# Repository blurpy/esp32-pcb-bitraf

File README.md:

# esp32-pcb-bitraf

ESP32 S2 Mini Development Board PCB created with KiCad 6 at Bitraf workshop, to be ordered from PCBWay.

Reference PCB for the workshop available here: https://github.com/jenschr/ESP32-workshop-files

Inspired by the official development board [ESP32-S2-DevKitM-1](https://docs.espressif.com/projects/esp-idf/en/v4.4/esp32s2/hw-reference/esp32s2/user-guide-devkitm-1-v1.html).

### Features

* Reset switch
* Boot switch for entering programming mode
* Power LED
* General purpose LED
* [DotStar LED](https://learn.adafruit.com/adafruit-dotstar-leds/overview)
* USB-C for power and programming
* Fits on a breadboard

### Board

### Schematic

### Bill of materials

Also available as an [interactive bom](https://blurpy.github.io/esp32-pcb-bitraf/bom/ibom.html).

| Item | Qty | Reference(s)   | Value                   | Type             | Footprint                              | Datasheet                                                                                                     |
|------|-----|----------------|-------------------------|------------------|----------------------------------------|---------------------------------------------------------------------------------------------------------------|
| 1    | 2   | BOOT1, RESET1  | SW_Push                 | Switch           | SW_SPST_Panasonic_EVQPL_3PL_5PL_PT_A08 | ~                                                                                                             |
| 2    | 4   | C1, C2, C3, C5 | 0.1uF                   | Capacitor        | 0603_1608Metric                        | ~                                                                                                             |
| 3    | 1   | C4             | 10uF                    | Capacitor        | 0805_2012Metric                        | ~                                                                                                             |
| 4    | 2   | D1, D2         | LED                     | LED              | 0603_1608Metric                        | ~                                                                                                             |
| 5    | 1   | D3             | APA102-2020             | DotStar LED      | APA102-2020                            | https://www.led-color.com/upload/201604/APA102-2020%20SMD%20LED.pdf                                           |
| 6    | 2   | J1, J3         | Conn_01x20_Male         | Header           | PinHeader_1x20_P2.54mm_Vertical        | ~                                                                                                             |
| 7    | 1   | J2             | USB_C_Receptacle_USB2.0 | USB-C Connector  | TYPE-C-31-M-12                         | https://www.usb.org/sites/default/files/documents/usb_type-c.zip                                              |
| 8    | 2   | R1, R2         | 10K                     | Resistor         | 0603_1608Metric                        | ~                                                                                                             |
| 9    | 2   | R3, R4         | 5.1K                    | Resistor         | 0603_1608Metric                        | ~                                                                                                             |
| 10   | 2   | R5, R6         | 33R                     | Resistor         | 0603_1608Metric                        | ~                                                                                                             |
| 11   | 2   | R7, R8         | 1K                      | Resistor         | 0603_1608Metric                        | ~                                                                                                             |
| 12   | 1   | U1             | ESP32-S2-M              | Microcontroller  | ESP32-S2-MINI-1-N4                     | https://www.espressif.com/sites/default/files/documentation/esp32-s2-mini-1_esp32-s2-mini-1u_datasheet_en.pdf |
| 13   | 1   | U2             | LM1117-3.3              | Linear Regulator | SOT-223                                | https://www.ti.com/lit/ds/symlink/lm1117.pdf                                                                  |

### Libraries

* [USB TYPE-C-31-M-12 from Korean Hroparts Elec @ LCSC](https://github.com/jenschr/USB-C-Connectors)
  *  Available here: https://lcsc.com/product-detail/USB-Connectors_Korean-Hroparts-Elec-TYPE-C-31-M-12_C165948.html
* [Espressif Systems ESP32-S2-MINI-1-N4](https://app.ultralibrarian.com/details/e7064ac7-afcb-11eb-9033-0a34d6323d74/Espressif-Systems/ESP32-S2-MINI-1-N4)
  * Symbol Pin Ordering: Functional
  * Footprint Units: English (mil)

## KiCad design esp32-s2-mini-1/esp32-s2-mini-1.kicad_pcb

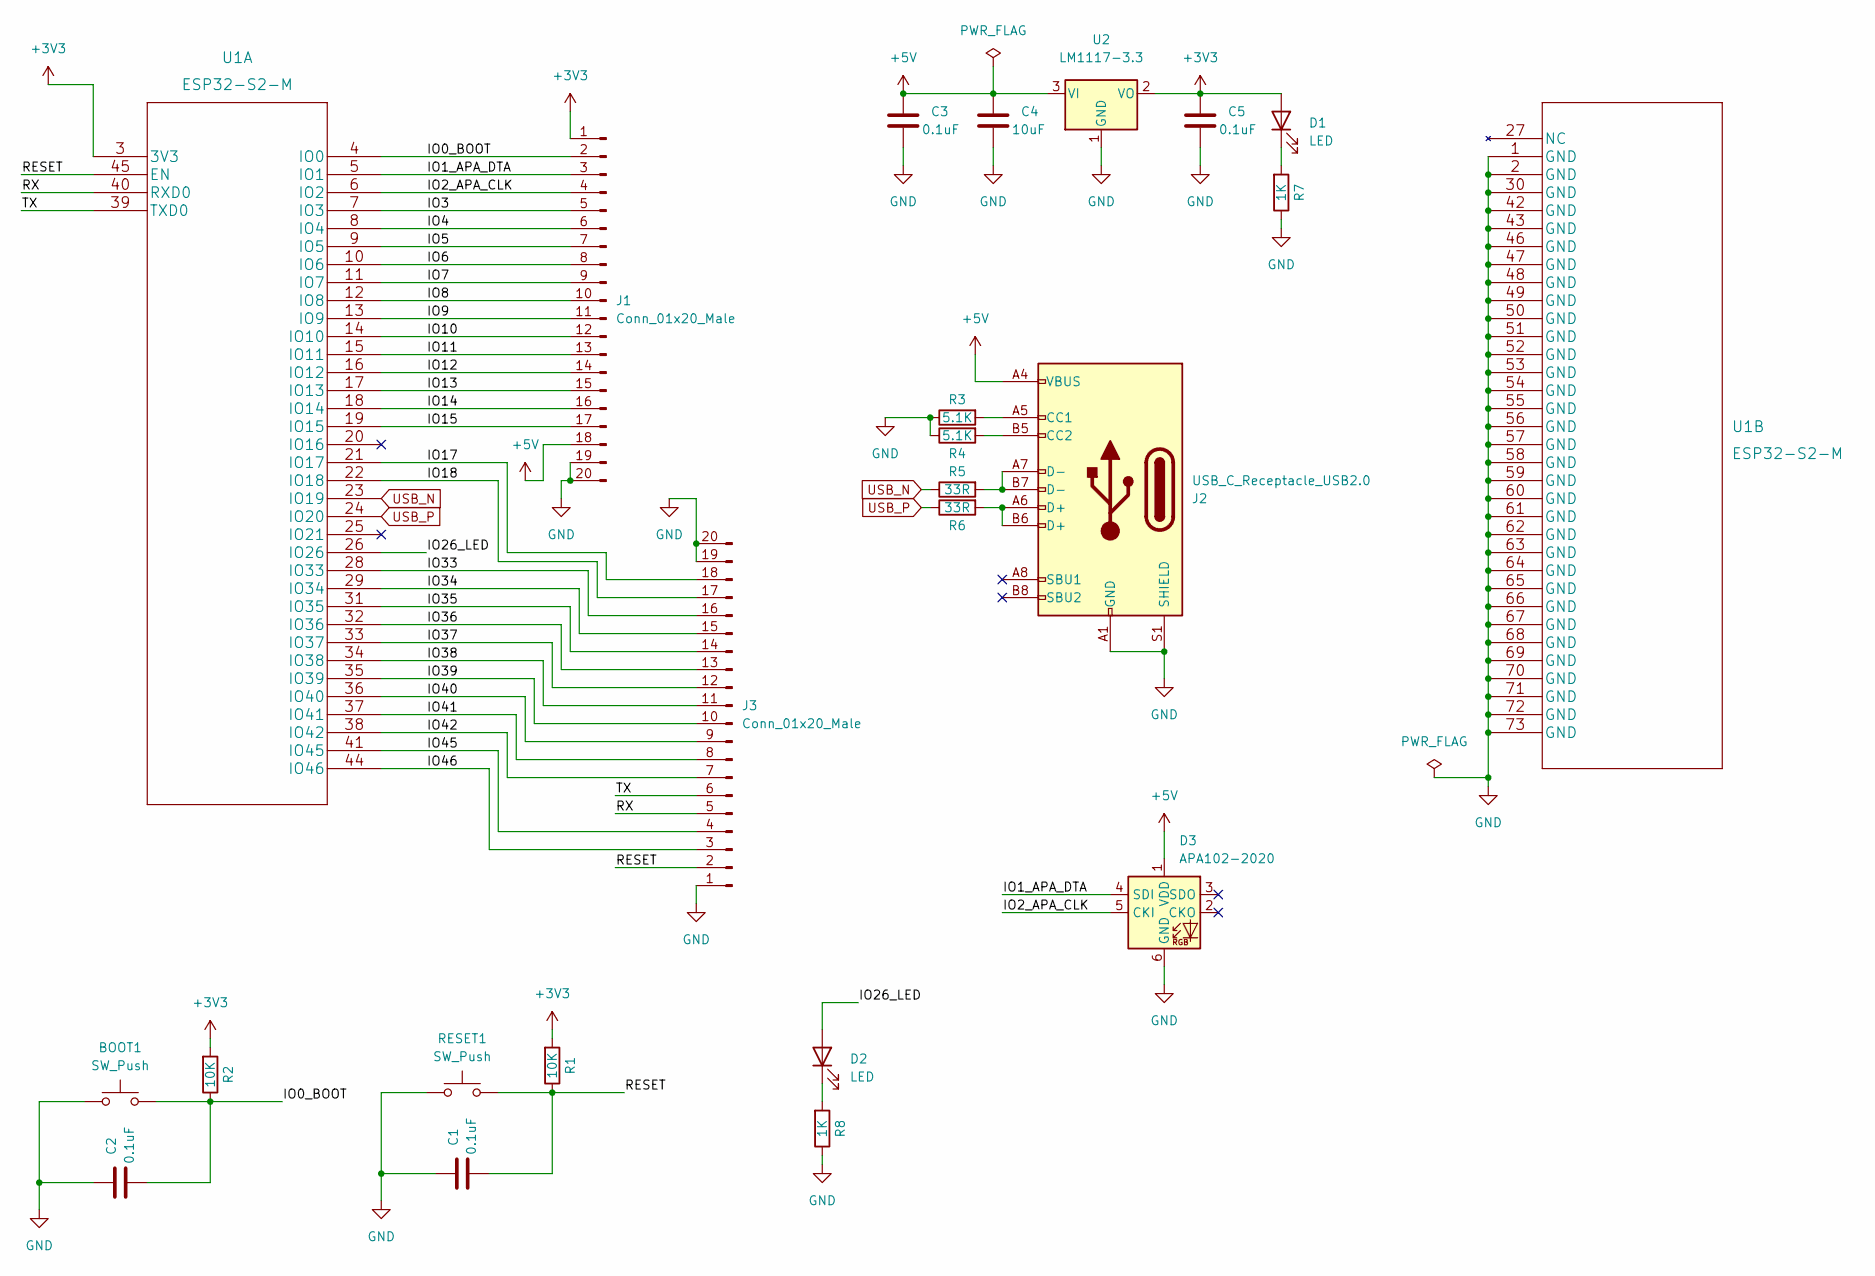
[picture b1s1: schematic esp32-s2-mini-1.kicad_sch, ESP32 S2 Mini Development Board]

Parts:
BOOT1: SW_Push; SW_SPST_Panasonic_EVQPL_3PL_5PL_PT_A08
C1, C2, C3, C5: 0.1uF; C_0603_1608Metric
C4: 10uF; C_0805_2012Metric
D1, D2: LED; LED_0603_1608Metric
D3: APA102-2020; LED-APA102-2020
J1, J3: Conn_01x20_Male; PinHeader_1x20_P2.54mm_Vertical
J2: USB_C_Receptacle_USB2.0; TYPE-C-31-M-12
R1, R2: 10K; R_0603_1608Metric
R3, R4: 5.1K; R_0603_1608Metric
R5, R6: 33R; R_0603_1608Metric
R7, R8: 1K; R_0603_1608Metric
RESET1: SW_Push; SW_SPST_Panasonic_EVQPL_3PL_5PL_PT_A08
U1: ESP32-S2-M; ESP32-S2-MINI-1-N4
U2: LM1117-3.3; SOT-223

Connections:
+3V3: C5.1, D1.2 (A), J1.1, R1.2, R2.2, U1.3 (3V3), U2.2 (VO)
+5V: C3.1, C4.1, D3.1 (VDD), J1.18, J2.A4 (VBUS), J2.A9 (VBUS), J2.B4 (VBUS), J2.B9 (VBUS), U2.3 (VI)
/IO0_BOOT: BOOT1.2, C2.2, J1.2, R2.1, U1.4 (IO0)
/IO1_APA_DTA: D3.4 (SDI), J1.3, U1.5 (IO1)
/IO2_APA_CLK: D3.5 (CKI), J1.4, U1.6 (IO2)
/IO3: J1.5, U1.7 (IO3)
/IO4: J1.6, U1.8 (IO4)
/IO5: J1.7, U1.9 (IO5)
/IO6: J1.8, U1.10 (IO6)
/IO7: J1.9, U1.11 (IO7)
/IO8: J1.10, U1.12 (IO8)
/IO9: J1.11, U1.13 (IO9)
/IO10: J1.12, U1.14 (IO10)
/IO11: J1.13, U1.15 (IO11)
/IO12: J1.14, U1.16 (IO12)
/IO13: J1.15, U1.17 (IO13)
/IO14: J1.16, U1.18 (IO14)
/IO15: J1.17, U1.19 (IO15)
/IO17: J3.18, U1.21 (IO17)
/IO18: J3.17, U1.22 (IO18)
/IO26_LED: D2.2 (A), U1.26 (IO26)
/IO33: J3.16, U1.28 (IO33)
/IO34: J3.15, U1.29 (IO34)
/IO35: J3.14, U1.31 (IO35)
/IO36: J3.13, U1.32 (IO36)
/IO37: J3.12, U1.33 (IO37)
/IO38: J3.11, U1.34 (IO38)
/IO39: J3.10, U1.35 (IO39)
/IO40: J3.9, U1.36 (IO40)
/IO41: J3.8, U1.37 (IO41)
/IO42: J3.7, U1.38 (IO42)
/IO45: J3.4, U1.41 (IO45)
/IO46: J3.3, U1.44 (IO46)
/RESET: C1.2, J3.2, R1.1, RESET1.2, U1.45 (EN)
/RX: J3.5, U1.40 (RXD0)
/TX: J3.6, U1.39 (TXD0)
GND: BOOT1.1, C1.1, C2.1, C3.2, C4.2, C5.2, D3.6 (GND), J1.19, J1.20, J2.A1 (GND), J2.A12 (GND), J2.B1 (GND), J2.B12 (GND), J2.S1 (SHIELD), J3.1, J3.19, J3.20, R3.1, R4.1, R7.1, R8.1, RESET1.1, U1.1 (GND), U1.2 (GND), U1.30 (GND), U1.42 (GND), U1.43 (GND), U1.46 (GND), U1.47 (GND), U1.48 (GND), U1.49 (GND), U1.50 (GND), U1.51 (GND), U1.52 (GND), U1.53 (GND), U1.54 (GND), U1.55 (GND), U1.56 (GND), U1.57 (GND), U1.58 (GND), U1.59 (GND), U1.60 (GND), U1.61 (GND), U1.62 (GND), U1.63 (GND), U1.64 (GND), U1.65 (GND), U1.66 (GND), U1.67 (GND), U1.68 (GND), U1.69 (GND), U1.70 (GND), U1.71 (GND), U1.72 (GND), U1.73 (GND), U2.1 (GND)
unnamed: D1.1 (K), R7.2
unnamed: D2.1 (K), R8.2
unnamed: J2.A5 (CC1), R3.2
unnamed: J2.A6 (D+), J2.B6 (D+), R6.2
unnamed: J2.A7 (D-), J2.B7 (D-), R5.2
unnamed: J2.B5 (CC2), R4.2
USB_N: R5.1, U1.23 (IO19)
USB_P: R6.1, U1.24 (IO20)

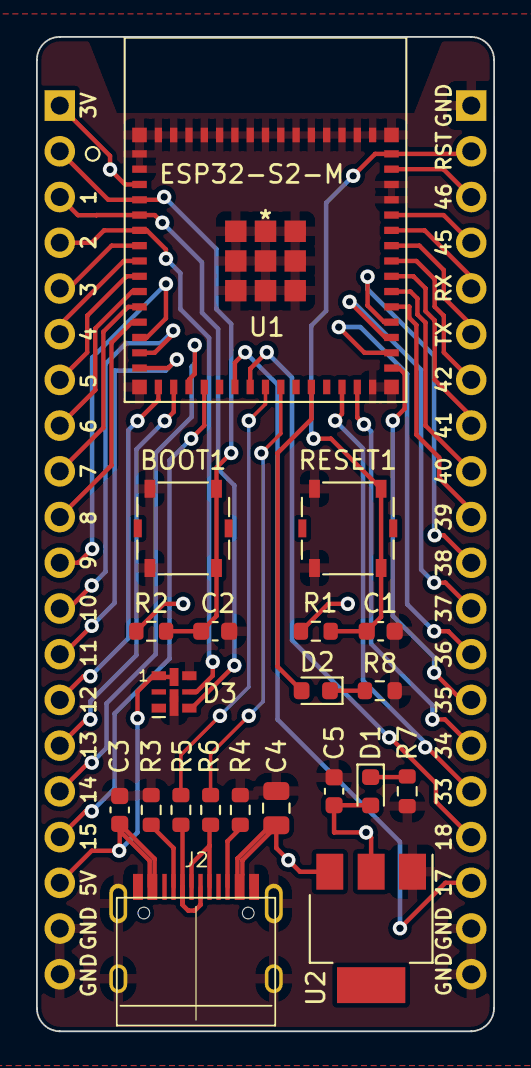
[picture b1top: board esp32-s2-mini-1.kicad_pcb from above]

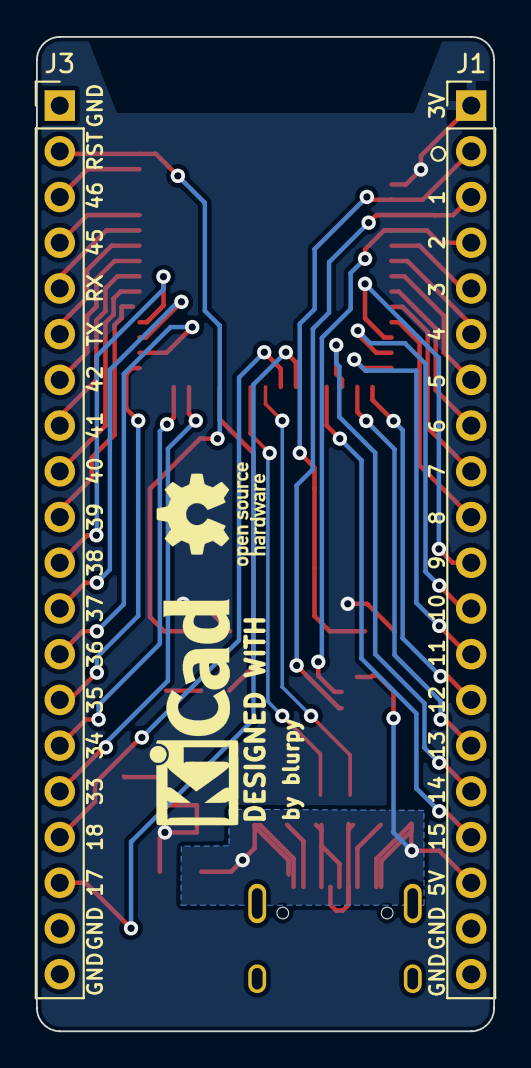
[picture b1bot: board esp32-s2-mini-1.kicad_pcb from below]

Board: 2 copper layers, 25.4 x 55.2 mm, 23 parts (2 on the bottom side), 45 nets.

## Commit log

2022-04-03 Adding files created during the workshop, and the required libraries
2022-04-03 Remove master from folder name of usb-c-connectors library
2022-04-03 Add info about libraries and parts
2022-04-03 Add more to gitignore
2022-04-03 Seems some labels were missing from original saves
2022-04-10 The basic structure of the pcb is ready. Pins are unconnected, and extra components are missing still.
2022-04-11 Add power LED
2022-04-12 Add controllable LED, dotstar LED, and connect everything
2022-04-13 Adding labels to pins in the schematic
2022-04-13 Tidy up schematic a bit
2022-04-13 Adding labels to half the pins on the pcb front
2022-04-13 Adding labels to the other half the pins on the pcb front
2022-04-13 Adding labels to the pins on the pcb back
2022-04-13 Add signature and logos to the pcb back
2022-04-14 Adding a title and date to the schematic
2022-04-14 Marking the logos on the back as "not in schematic" to avoid them being removed when updating the pcb from schematic
2022-04-14 Changing clearance from 0.2mm to 0.18mm since it's used by the dotstar LED and it should work
2022-04-14 Add gerbers and drill files
2022-04-14 Updated readme with pictures and bom
2022-04-14 Adjusting size of images and adding links to full size
2022-07-13 Adding interactive bom
2022-07-13 Fix table formatting
2022-07-13 Add link to interactive bom
2022-07-13 Add link to USB-C connector

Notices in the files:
parts and their libraries:
Copyright 2021 Accelerated Designs. All rights reserved.
